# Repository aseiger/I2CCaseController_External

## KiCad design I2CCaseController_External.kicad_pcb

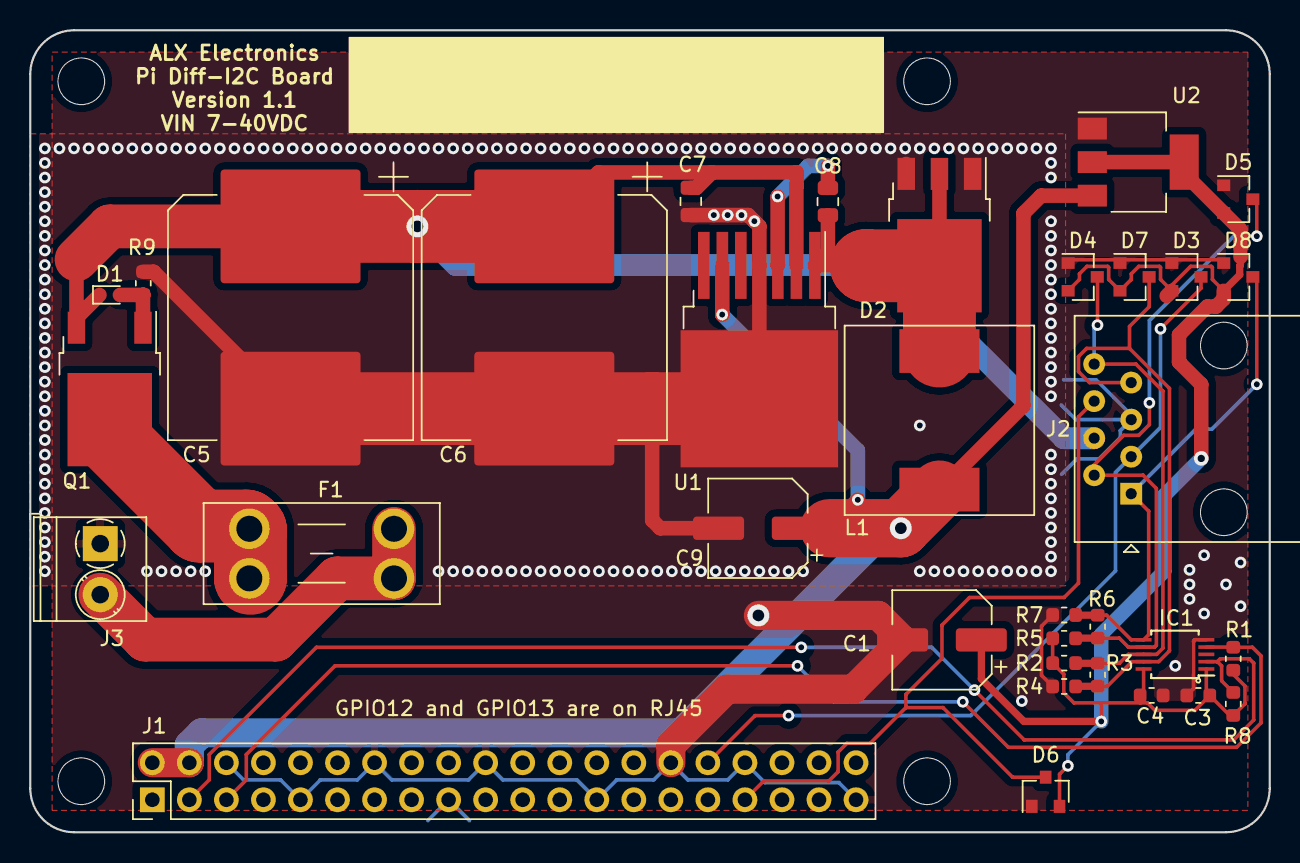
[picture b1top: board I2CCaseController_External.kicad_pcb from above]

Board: 2 copper layers, 85.0 x 55.0 mm, 38 parts (0 on the bottom side), 18 nets.

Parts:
C1, C9: 330uF; CP_Elec_6.3x7.7
C3: 0.1uF; C_0603_1608Metric
C4: 1uF; C_0603_1608Metric
C5, C6: 100uF; CP_Elec_16x17.5
C7: 100nF; C_0805_2012Metric
C8: 10nF; C_0805_2012Metric
D1: DZ2S120X0L; D_SOD-523
D2: SBRD10200; TO-252-3_TabPin2
D3, D4, D5, D6, D7, D8: BAT54S; SOT-23
F1: Fuse; Fuseholder_Blade_Mini_Keystone_3568
H1, H2, H3, H4: MountingHole; MountingHole_3.2mm_M3
IC1: PCA9615DPJ; TSSOP-10_3x3mm_P0.5mm
J1: Raspberry_Pi_2_3; PinHeader_2x20_P2.54mm_Vertical
J2: 8P8C; RJ45_Amphenol_54602-x08_Horizontal
J3: Conn_01x02; TerminalBlock_Phoenix_PT-1,5-2-3.5-H_1x02_P3.50mm_Horizontal
L1: 15uH; Coilcraft_MSS1210
Q1: SUD19P06-60; TO-252-2
R1, R8: 4.7k; R_0603_1608Metric
R2, R4, R5, R7: 390; R_0603_1608Metric
R3, R6: 100; R_0603_1608Metric
R9: 12K; R_0603_1608Metric
U1: LM2678; TO-263-7_TabPin4
U2: LM1117-3.3; SOT-223-3_TabPin2

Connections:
+3.3VP: C1.1, C3.1, C4.1, D3.2, D4.2, D5.2, D6.2, D7.2, D8.2, IC1.1, IC1.10, R1.1, R2.1, R5.1, R8.1, U2.2
+3V3: J1.1, J1.17
+5V: C9.1, J1.2, J1.4, L1.2, U1.6, U2.3
+VDC: C5.1, C6.1, C7.1, D1.1, J2.4, Q1.3, U1.2
/DSCL+: D5.3, IC1.7, J2.2, R5.2, R6.1
/DSCL-: D8.3, IC1.6, J2.1, R6.2, R7.1
/DSDA+: D4.3, IC1.8, J2.8, R2.2, R3.1
/DSDA-: D7.3, IC1.9, J2.7, R3.2, R4.1
/SCL: IC1.4, J1.5, R1.2
/SDA: IC1.2, J1.3, R8.2
GND: C1.2, C3.2, C4.2, C5.2, C6.2, C7.2, C9.2, D2.1, D2.3, D3.1, D4.1, D5.1, D6.1, D7.1, D8.1, IC1.5, J1.6, J1.9, J1.14, J1.20, J1.25, J1.30, J1.34, J1.39, J2.5, J3.1, R4.2, R7.2, R9.2, U1.4, U2.1
unnamed: C8.1, D2.2, L1.1, U1.1
unnamed: C8.2, U1.3
unnamed: D1.2, Q1.1, R9.1
unnamed: D3.3, J1.32, J2.3
unnamed: D6.3, J1.33, J2.6
unnamed: F1.1, Q1.2
unnamed: F1.2, J3.2

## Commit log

2021-03-28 Initial commit of recovered schematics
2021-03-28 Updated Library Refs
2021-03-28 Added Recovered PCB File
